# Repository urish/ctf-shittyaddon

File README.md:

# Minimal Shitty Add-On with Capture The Flag Challenge

Copyright (C) 2019, Uri Shaked. Released under the MIT license.

[__Learn more in the blog post: Capture The Flag Shitty Add-On__](https://blog.wokwi.com/capture-the-flag-shitty-add-on/?utm_source=github)

## Hardware

The [ctf-shittyaddon board](pcb/) includes the following hardware:

1. ATtiny85 Processor
2. A [ShittyAddon V1](https://twitter.com/MrRobotBadge/status/962043056781324289) connector 
3. Reset button
4. Red LED connected to ATtiny85's pin 6 (PB1)

You can also hack a simplified version on a breadboard:

## Firmware

Compile the firmware using the Arduino IDE:

1. Install [ATTiny Core](https://github.com/damellis/attiny)
2. Install the [TinyWire Library](https://github.com/lucullusTheOnly/TinyWire)
3. Configure Arduino IDE as follows:
   - Board: ATtiny25/45/85
   - Processor: ATtiny85
   - Clock: Internal 8 MHz
4. Set the fuses of the chip to enable self programming (`SELFPRGEN=1`). 
   This can be done using `avrdude`:
   ```bash
   avrdude -pattiny85 -cusbtiny -e -Uefuse:w:0xfe:m -Uhfuse:w:0xdf:m -Ulfuse:w:0xe2:m
   ```

When building your own firmware, replace `SECRET` in the string `"$FLAG:SECRET"` 
with your secret value (the flag).

## The Challenge

The [firmware code](ctf-firmware/ctf-firmware.ino) implements an I2C slave listening on address 0x23.

The challenge consists of several milestones of increasing difficulty:

1. Make the red LED light
2. Find the secret flag value (it starts with the string "$FLAG:")
3. Make the red LED blink by executing code directly on the ATTiny85
4. Replace the secret flag with a new value without bricking the board

All the above milestones can be achieved through I2C communication with
the chip.

For more information, [check out the blog post](https://blog.wokwi.com/capture-the-flag-shitty-add-on/?utm_source=github)

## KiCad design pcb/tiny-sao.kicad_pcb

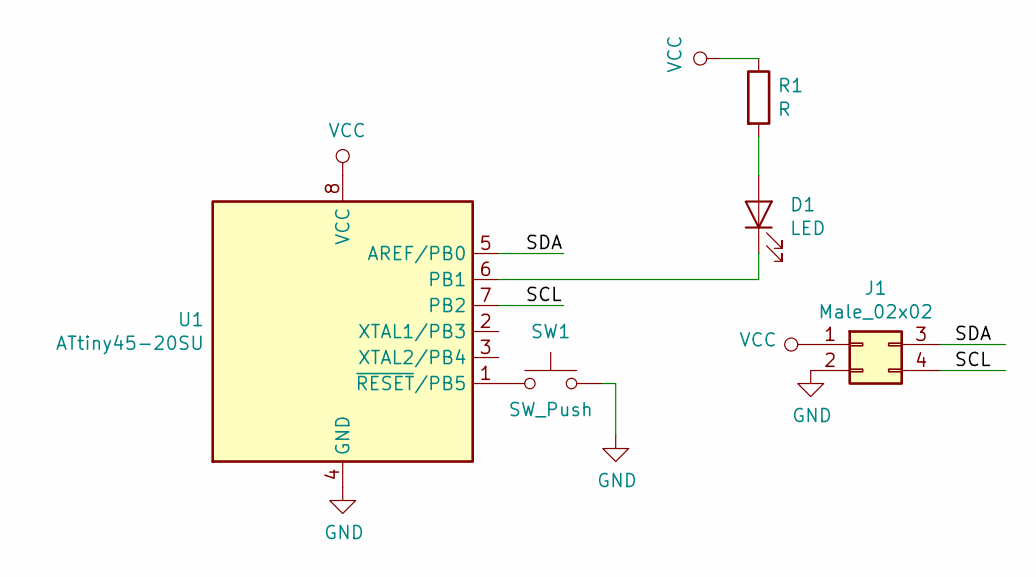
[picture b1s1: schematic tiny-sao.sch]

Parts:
D1: LED; LED_0603_1608Metric
J1: Male_02x02; PinHeader_2x02_P2.54mm_Vertical
R1: R; R_0603_1608Metric
SW1: SW_Push; TACTILE-SWITCH-1101NE
U1: ATtiny45-20SU; SOIJ-8_5.3x5.3mm_P1.27mm

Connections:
/SCL: J1.4, U1.7 (PB2)
/SDA: J1.3, U1.5 (AREF/PB0)
GND: J1.2, SW1.2, U1.4 (GND)
unnamed: D1.1 (K), U1.6 (PB1)
unnamed: D1.2 (A), R1.2
unnamed: SW1.1, U1.1 (~RESET~/PB5)
VCC: J1.1, R1.1, U1.8 (VCC)

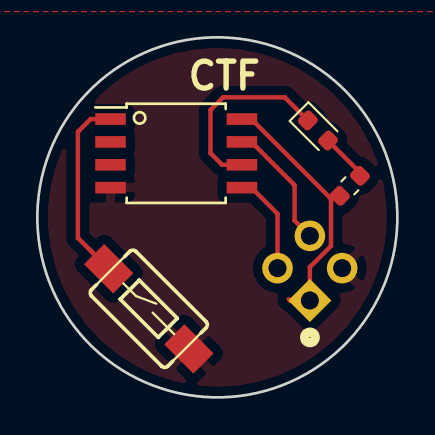
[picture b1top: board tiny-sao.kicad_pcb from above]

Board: 2 copper layers, 20.0 x 20.0 mm, 5 parts (1 on the bottom side), 7 nets.

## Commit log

2019-08-28 fix(pcb): SCL and SDA were crossed
2019-08-28 feat(pcb): indicate VCC with a circle
    per ShittyAddon V1 standard
2019-10-30 doc: link to blog post + add photos
2019-11-02 fix(firmware): add missing typecast
    Makes the compiler happy, see https://twitter.com/manekinekko/status/1190696892910444544 for details
